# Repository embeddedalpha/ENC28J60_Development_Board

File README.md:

# ENC28J60 Development Board

### 1.

### 2.

### 3.

### 4.

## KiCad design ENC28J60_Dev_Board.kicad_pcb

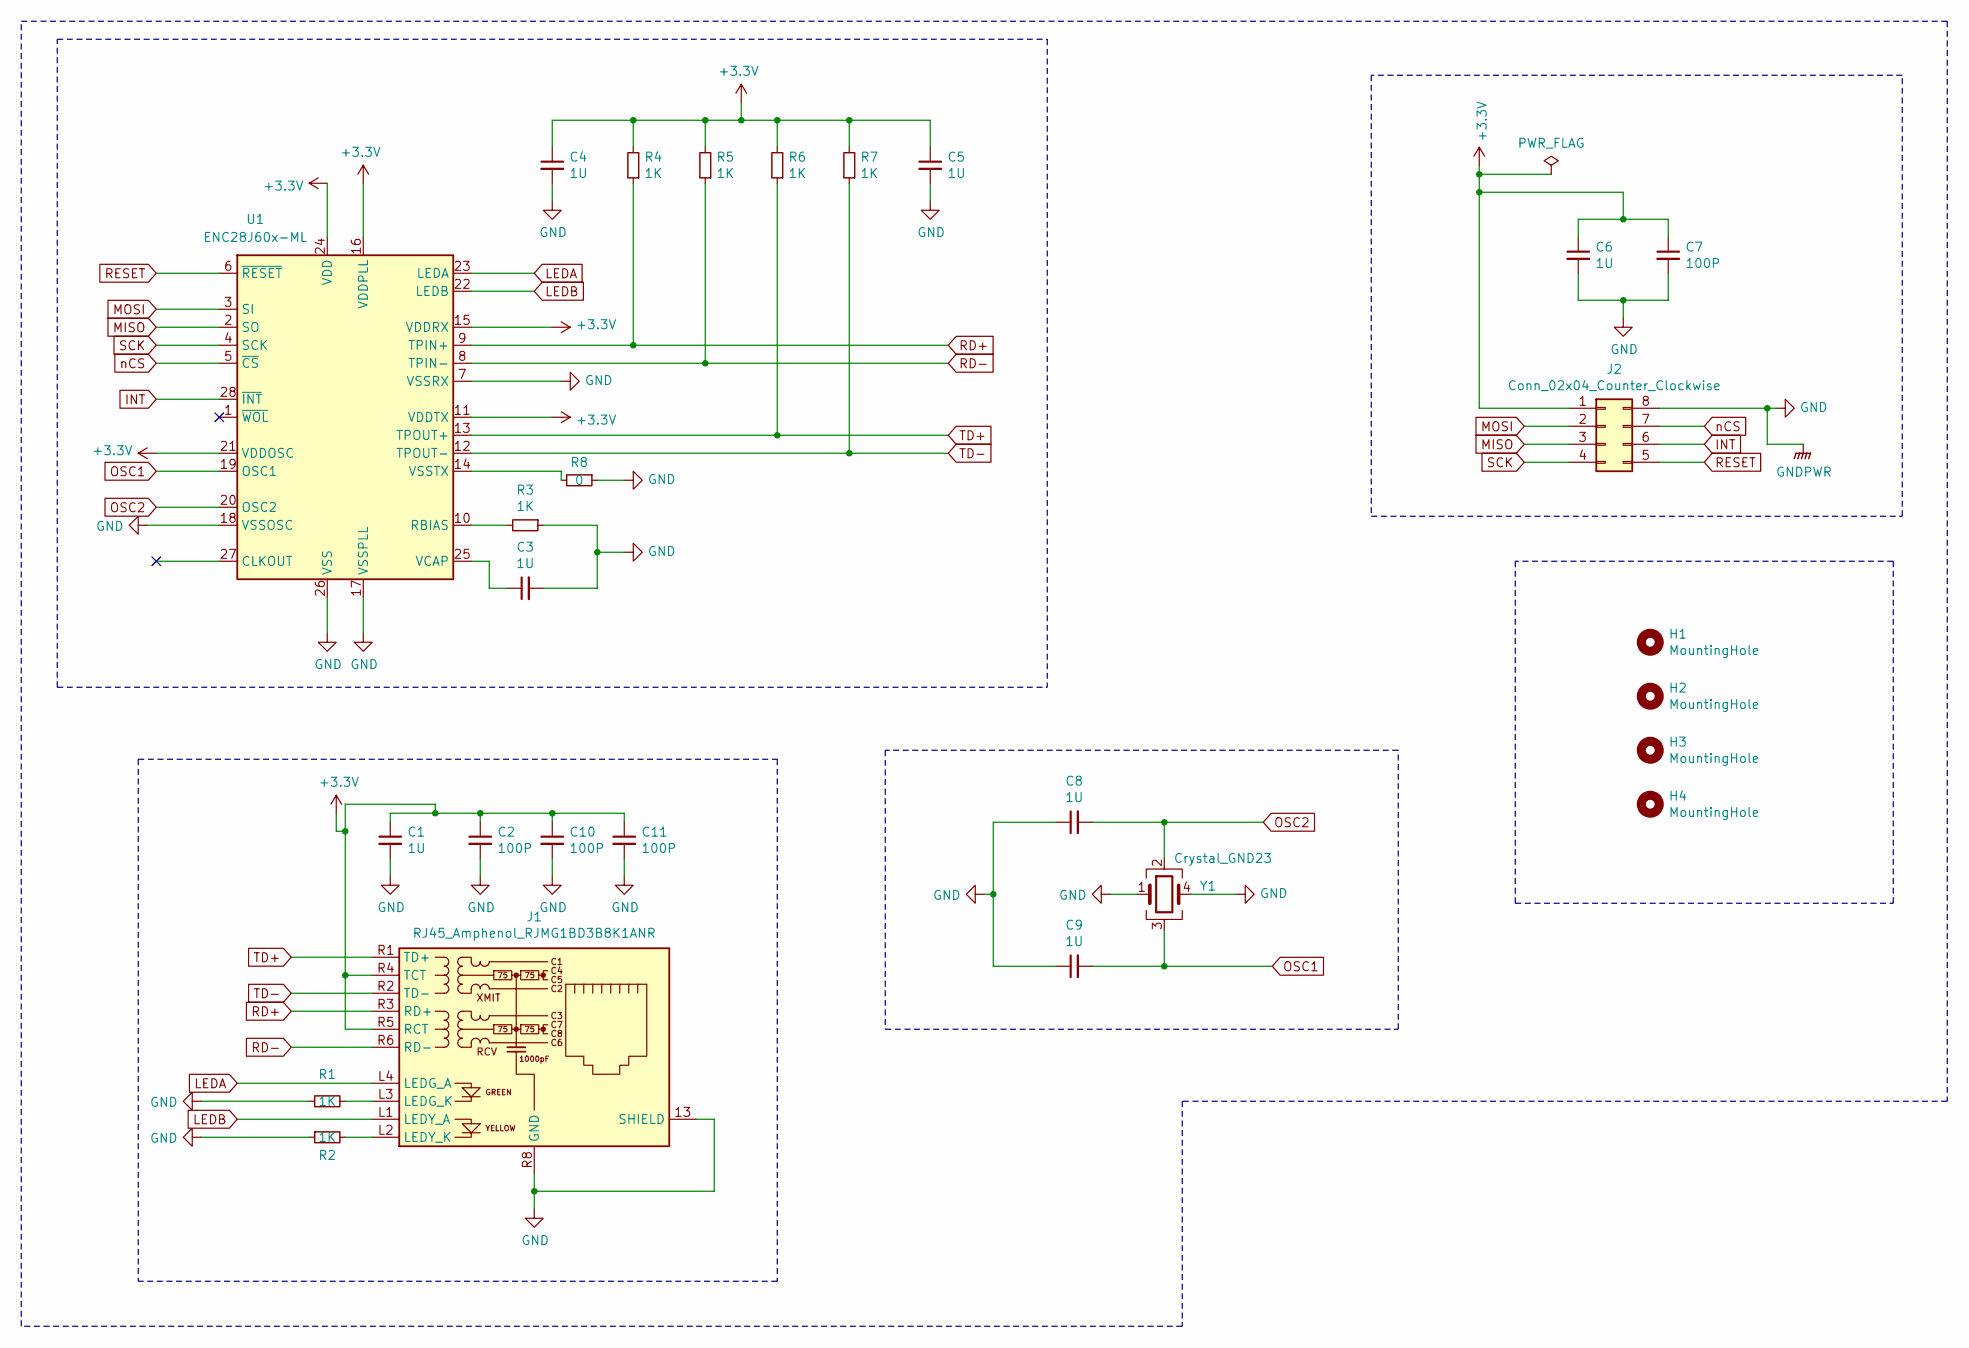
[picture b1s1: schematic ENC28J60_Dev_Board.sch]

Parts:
C1, C3, C4, C5, C6, C8, C9: 1U; C_0603_1608Metric
C2, C7, C10, C11: 100P; C_0603_1608Metric
H1, H2, H3, H4: MountingHole; MountingHole_3.2mm_M3_Pad_Via
J1: RJ45_Amphenol_RJMG1BD3B8K1ANR
J2: Conn_02x04_Counter_Clockwise; PinHeader_2x04_P2.54mm_Horizontal
R1, R2, R3, R4, R5, R6, R7: 1K; R_0603_1608Metric
R8: 0; R_0603_1608Metric
U1: ENC28J60x-ML; QFN-28-1EP_6x6mm_P0.65mm_EP4.25x4.25mm
Y1: Crystal_GND23; Crystal_SMD_SeikoEpson_FA238-4Pin_3.2x2.5mm

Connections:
+3V3: C1.1, C2.1, C4.1, C5.1, C6.1, C7.1, C10.1, C11.1, J1.R4 (TCT), J1.R5 (RCT), J2.1, R4.2, R5.2, R6.2, R7.2, U1.11 (VDDTX), U1.15 (VDDRX), U1.16 (VDDPLL), U1.21 (VDDOSC), U1.24 (VDD)
GND: C1.2, C2.2, C3.2, C4.2, C5.2, C6.2, C7.2, C8.1, C9.1, C10.2, C11.2, J1.13 (SHIELD), J1.R8 (GND), J2.8, R1.1, R2.1, R3.1, R8.1, U1.7 (VSSRX), U1.17 (VSSPLL), U1.18 (VSSOSC), U1.26 (VSS), Y1.1, Y1.4
INT: J2.6, U1.28 (~INT)
LEDA: J1.L4 (LEDG_A), U1.23 (LEDA)
LEDB: J1.L1 (LEDY_A), U1.22 (LEDB)
MISO: J2.3, U1.2 (SO)
MOSI: J2.2, U1.3 (SI)
unnamed: C3.1, U1.25 (VCAP)
unnamed: J1.L2 (LEDY_K), R2.2
unnamed: J1.L3 (LEDG_K), R1.2
unnamed: R3.2, U1.10 (RBIAS)
unnamed: R8.2, U1.14 (VSSTX)
OSC1: C9.2, U1.19 (OSC1), Y1.3
OSC2: C8.2, U1.20 (OSC2), Y1.2
RD+: J1.R3 (RD+), R4.1, U1.9 (TPIN+)
RD-: J1.R6 (RD-), R5.1, U1.8 (TPIN-)
RESET: J2.5, U1.6 (~RESET)
SCK: J2.4, U1.4 (SCK)
TD+: J1.R1 (TD+), R6.1, U1.13 (TPOUT+)
TD-: J1.R2 (TD-), R7.1, U1.12 (TPOUT-)
nCS: J2.7, U1.5 (~CS)

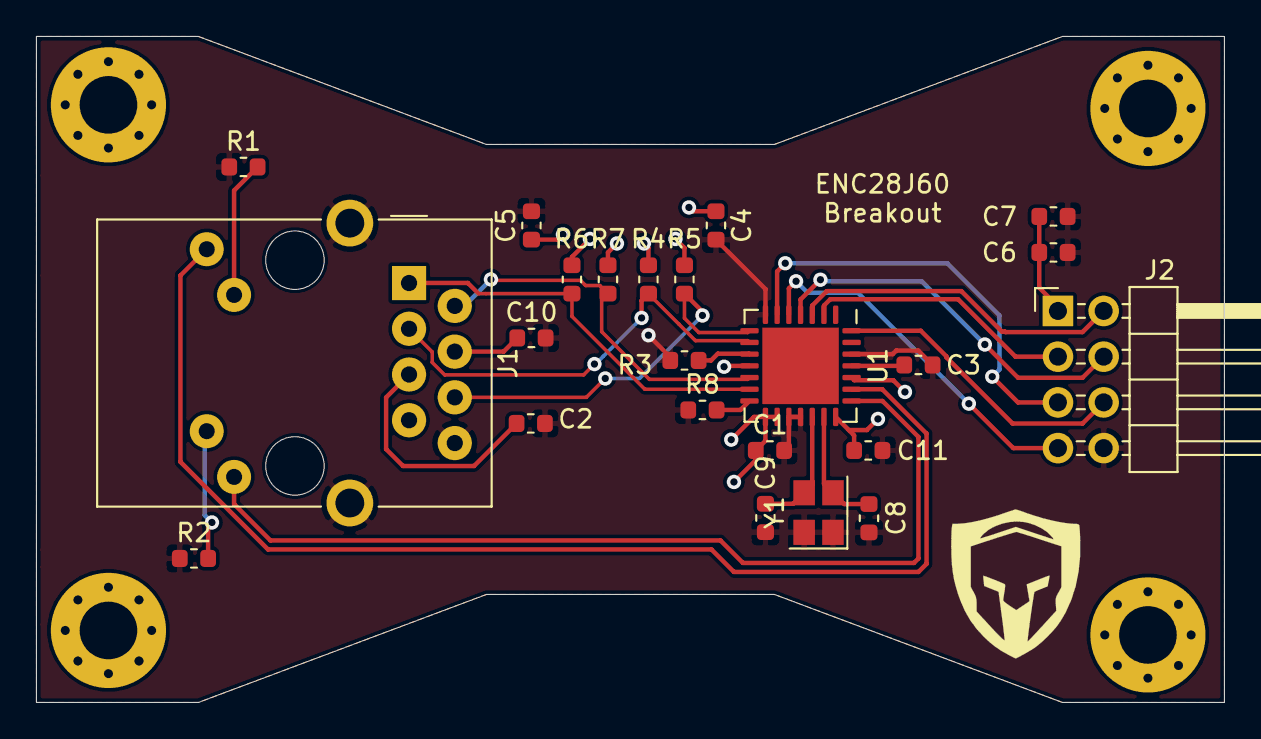
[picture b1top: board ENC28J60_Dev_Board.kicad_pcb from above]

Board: 2 copper layers, 66.0 x 37.0 mm, 27 parts (0 on the bottom side), 21 nets.

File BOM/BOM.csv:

"Id";"Designator";"Package";"Quantity";"Designation";"Supplier and ref";
1;"G***";"Company_Logo1";1;"LOGO";;;
2;"C1,C3,C4,C5,C6,C8,C9";"C_0603_1608Metric";7;"1U";;;
3;"C2,C7,C10,C11";"C_0603_1608Metric";4;"100P";;;
4;"H1,H2,H3,H4";"MountingHole_3.2mm_M3_Pad_Via";4;"MountingHole";;;
5;"J1";"RJ45_Amphenol_RJMG1BD3B8K1ANR";1;"RJ45_Amphenol_RJMG1BD3B8K1ANR";;;
6;"J2";"PinHeader_2x04_P2.54mm_Horizontal";1;"Conn_02x04_Counter_Clockwise";;;
7;"R1,R2,R3,R4,R5,R6,R7";"R_0603_1608Metric";7;"1K";;;
8;"R8";"R_0603_1608Metric";1;"0";;;
9;"U1";"QFN-28-1EP_6x6mm_P0.65mm_EP4.25x4.25mm";1;"ENC28J60x-ML";;;
10;"Y1";"Crystal_SMD_SeikoEpson_FA238-4Pin_3.2x2.5mm";1;"Crystal_GND23";;;

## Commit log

2020-09-26 Create txt
